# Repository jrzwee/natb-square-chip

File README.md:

# NATB
PCB Badge/Sticker

## Usage
This PCB should be manufactured in 0.4 mm or 0.6 mm.

## Renders

## License
[CERN-OHL-S](https://ohwr.org/cern_ohl_s_v2.pdf)

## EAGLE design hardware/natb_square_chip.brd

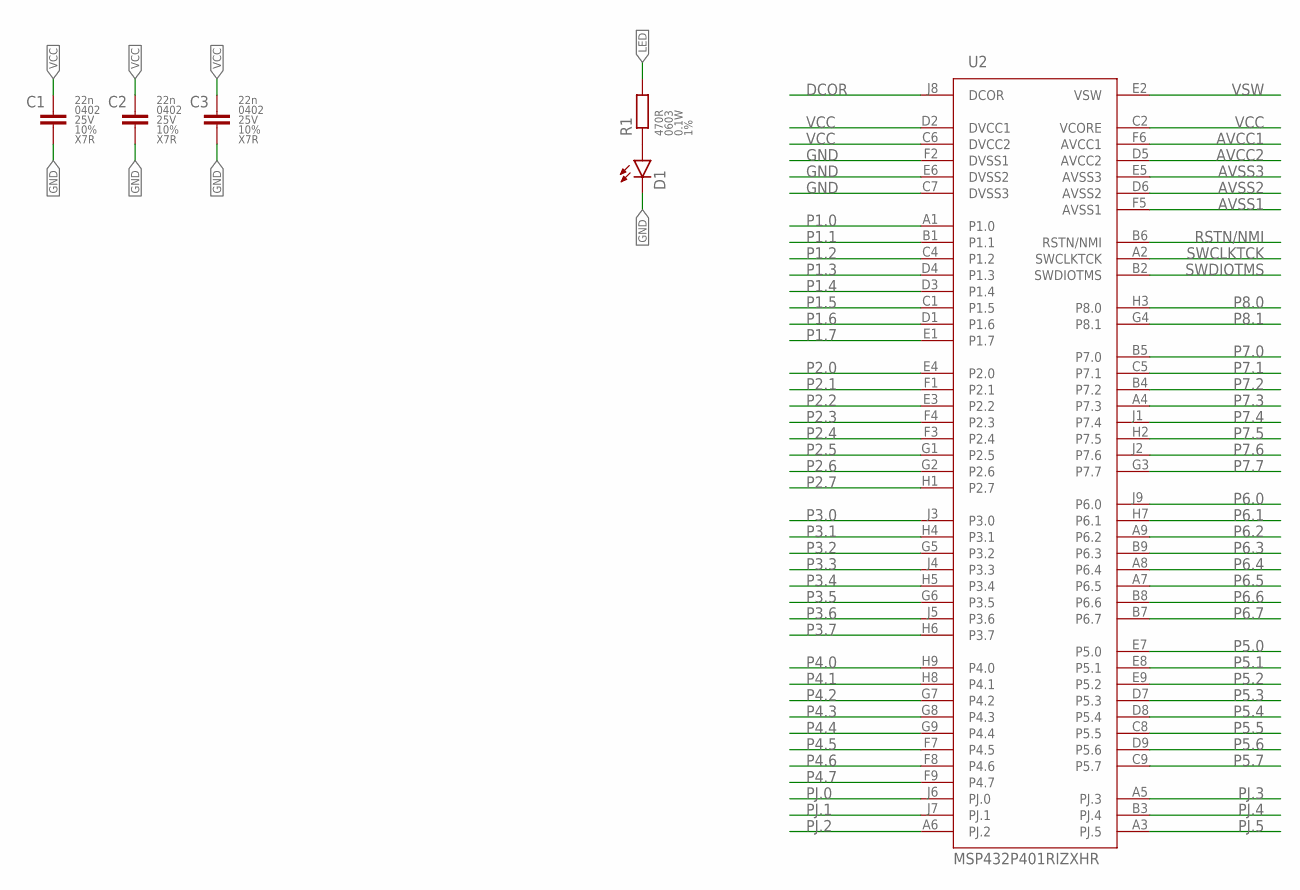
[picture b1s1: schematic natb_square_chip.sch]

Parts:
C1, C2, C3: 22n; C0402
D1: LEDCHIP-LED0603; CHIP-LED0603
R1: 470R; R0603
U2: MSP432P401RIZXHR; BGA80

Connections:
AVCC1: U2.F6 (AVCC1)
AVCC2: U2.D5 (AVCC2)
AVSS1: U2.F5 (AVSS1)
AVSS2: U2.D6 (AVSS2)
AVSS3: U2.E5 (AVSS3)
DCOR: U2.J8 (DCOR)
GND: C1.2, C2.2, C3.2, D1.C, U2.C7 (DVSS3), U2.E6 (DVSS2), U2.F2 (DVSS1)
LED: R1.2
unnamed: D1.A, R1.1
P1.0: U2.A1 (P1.0)
P1.1: U2.B1 (P1.1)
P1.2: U2.C4 (P1.2)
P1.3: U2.D4 (P1.3)
P1.4: U2.D3 (P1.4)
P1.5: U2.C1 (P1.5)
P1.6: U2.D1 (P1.6)
P1.7: U2.E1 (P1.7)
P2.0: U2.E4 (P2.0)
P2.1: U2.F1 (P2.1)
P2.2: U2.E3 (P2.2)
P2.3: U2.F4 (P2.3)
P2.4: U2.F3 (P2.4)
P2.5: U2.G1 (P2.5)
P2.6: U2.G2 (P2.6)
P2.7: U2.H1 (P2.7)
P3.0: U2.J3 (P3.0)
P3.1: U2.H4 (P3.1)
P3.2: U2.G5 (P3.2)
P3.3: U2.J4 (P3.3)
P3.4: U2.H5 (P3.4)
P3.5: U2.G6 (P3.5)
P3.6: U2.J5 (P3.6)
P3.7: U2.H6 (P3.7)
P4.0: U2.H9 (P4.0)
P4.1: U2.H8 (P4.1)
P4.2: U2.G7 (P4.2)
P4.3: U2.G8 (P4.3)
P4.4: U2.G9 (P4.4)
P4.5: U2.F7 (P4.5)
P4.6: U2.F8 (P4.6)
P4.7: U2.F9 (P4.7)
P5.0: U2.E7 (P5.0)
P5.1: U2.E8 (P5.1)
P5.2: U2.E9 (P5.2)
P5.3: U2.D7 (P5.3)
P5.4: U2.D8 (P5.4)
P5.5: U2.C8 (P5.5)
P5.6: U2.D9 (P5.6)
P5.7: U2.C9 (P5.7)
P6.0: U2.J9 (P6.0)
P6.1: U2.H7 (P6.1)
P6.2: U2.A9 (P6.2)
P6.3: U2.B9 (P6.3)
P6.4: U2.A8 (P6.4)
P6.5: U2.A7 (P6.5)
P6.6: U2.B8 (P6.6)
P6.7: U2.B7 (P6.7)
P7.0: U2.B5 (P7.0)
P7.1: U2.C5 (P7.1)
P7.2: U2.B4 (P7.2)
P7.3: U2.A4 (P7.3)
P7.4: U2.J1 (P7.4)
P7.5: U2.H2 (P7.5)
P7.6: U2.J2 (P7.6)
P7.7: U2.G3 (P7.7)
P8.0: U2.H3 (P8.0)
P8.1: U2.G4 (P8.1)
PJ.0: U2.J6 (PJ.0)
PJ.1: U2.J7 (PJ.1)
PJ.2: U2.A6 (PJ.2)
PJ.3: U2.A5 (PJ.3)
PJ.4: U2.B3 (PJ.4)
PJ.5: U2.A3 (PJ.5)
RSTN/NMI: U2.B6 (RSTN/NMI)
SWCLKTCK: U2.A2 (SWCLKTCK)
SWDIOTMS: U2.B2 (SWDIOTMS)
VCC: C1.1, C2.1, C3.1, U2.C2 (VCORE), U2.C6 (DVCC2), U2.D2 (DVCC1)
VSW: U2.E2 (VSW)

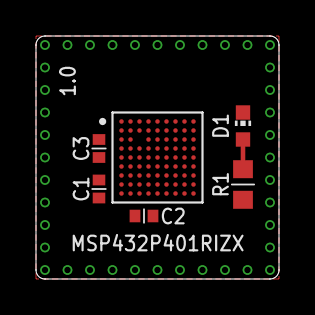
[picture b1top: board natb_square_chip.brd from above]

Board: 2 copper layers, 13.5 x 13.5 mm, 7 parts (1 on the bottom side), 3 nets.

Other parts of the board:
U$1: QR-NATB-10

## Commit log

2020-04-29 Creation of PCB
2020-04-29 Changed color of soldermask to black
2020-04-29 Added Readme, Renders and Gerbers
2020-04-29 Fixed Renders
2020-05-08 Changed version history on silkscreen
2021-01-24 Changes SOIC and BGA
2021-01-24 Changed parts and added qr code
2021-01-24 Update LICENSE
2021-01-24 Updated renders
